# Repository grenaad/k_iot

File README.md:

View this project on [CADLAB.io](https://cadlab.io/project/23303). 

# k_iot
# k_iot

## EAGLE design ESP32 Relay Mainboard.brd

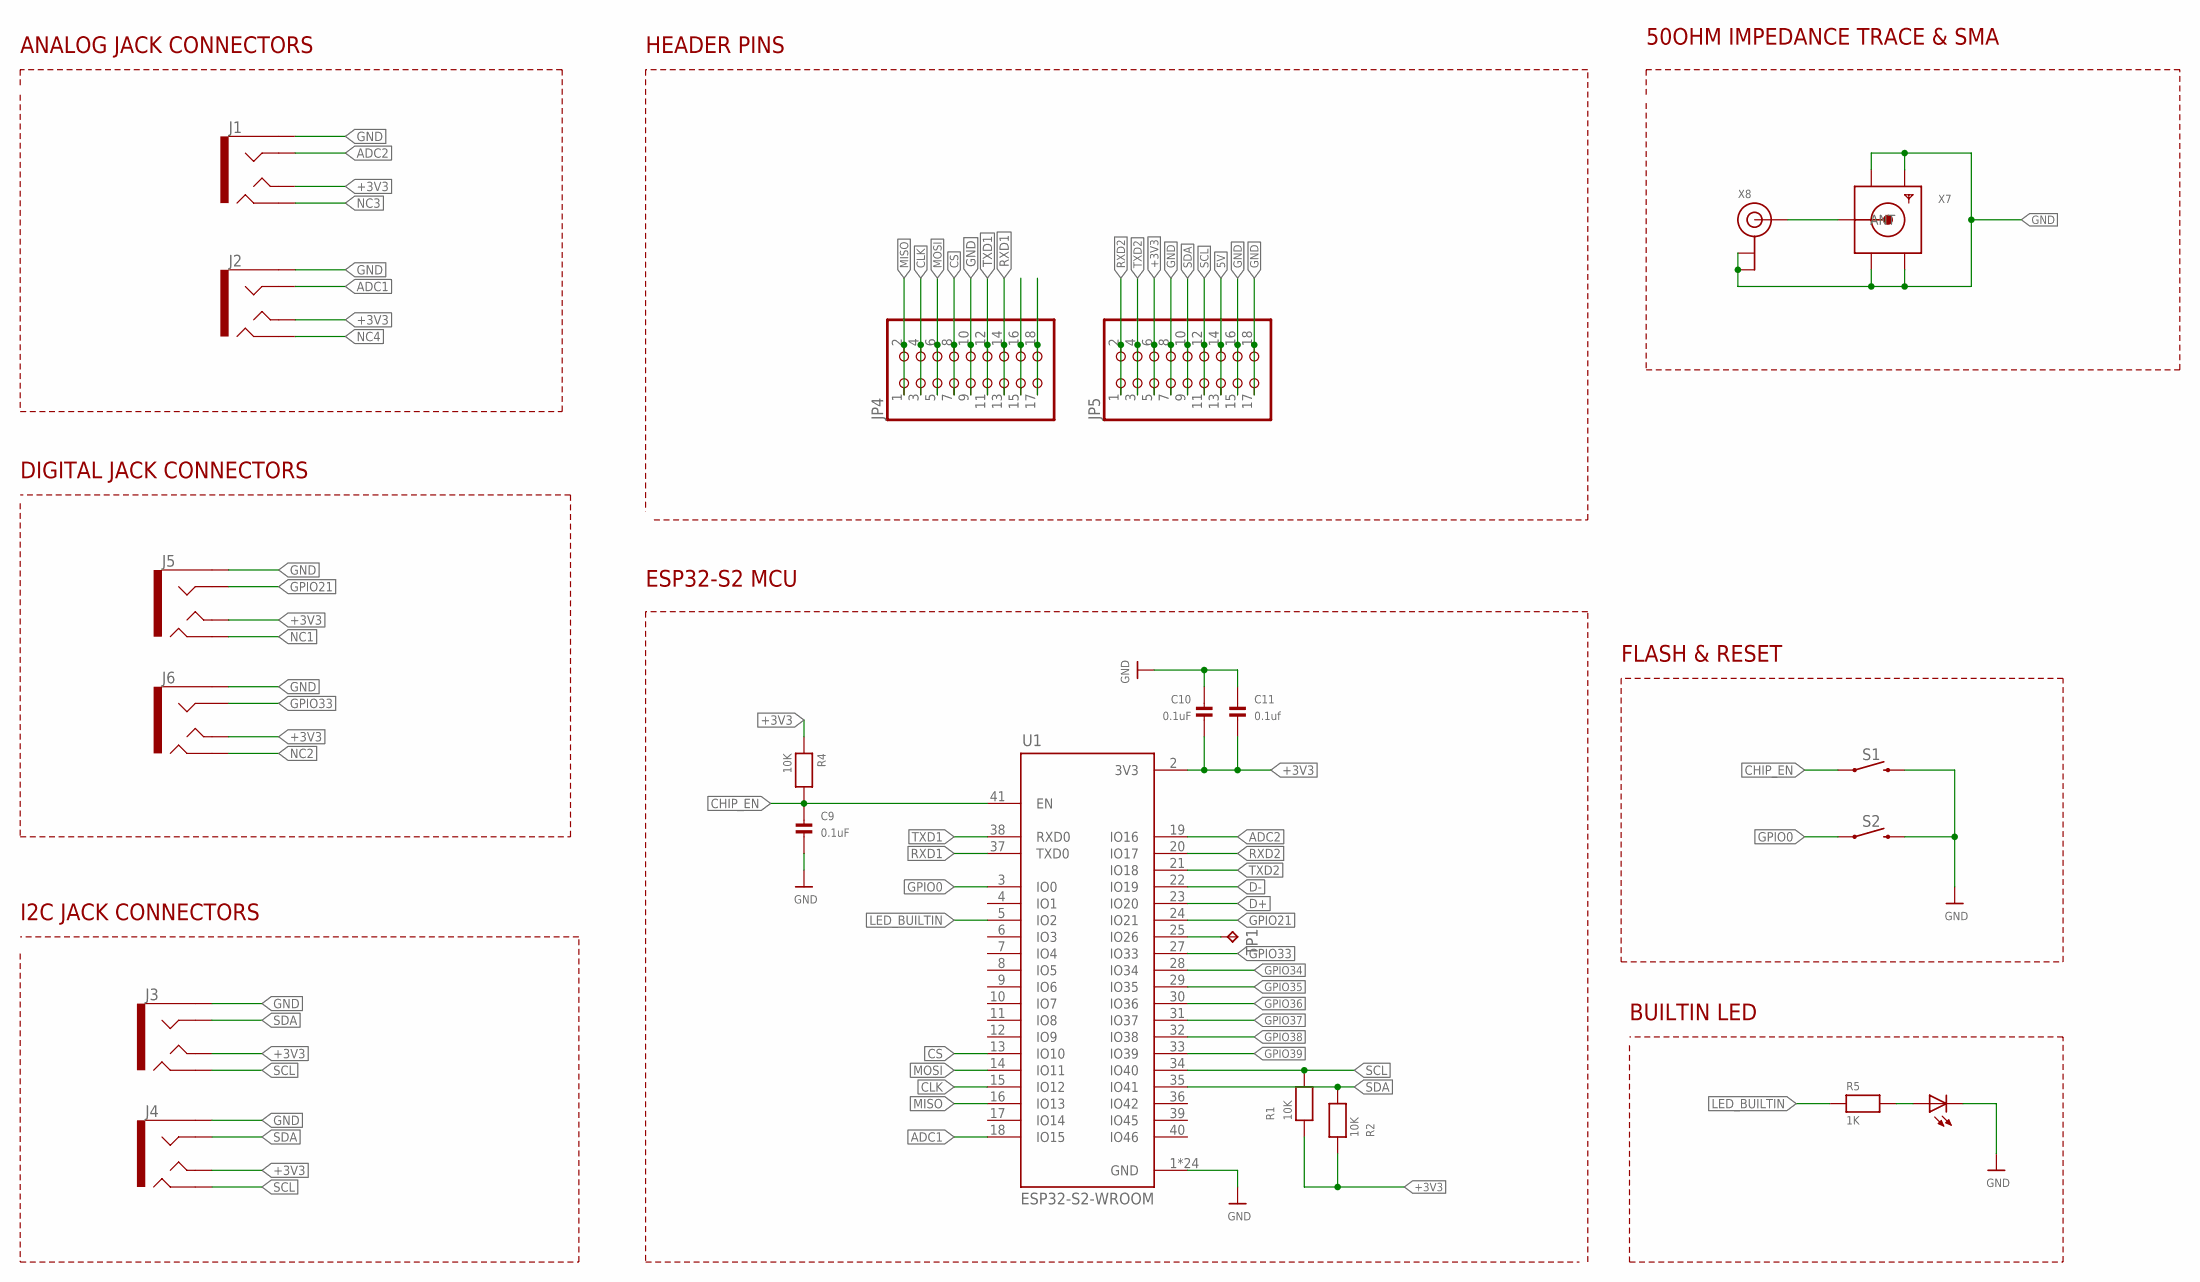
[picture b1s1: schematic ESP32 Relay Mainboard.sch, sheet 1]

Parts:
C9, C10: 0.1uF; 0805
C11: 0.1uf; 0805
J1, J2, J3, J4, J5, J6: AUDIO_JACK_TRRSSMD_RA; AUDIO_JACK_3.5MM_TRRS_SMD_RA
JP4, JP5: PINHD-2X9-BIG; 2X09-BIG
LED1: LEDCHIPLED_0805; CHIPLED_0805
R1, R2, R4: 10K; 0805
R5: 1K; 0805
S1, S2: MOMENTARY-SWITCH-SPST-SMD-5.2-REDUNDANT; TACTILE_SWITCH_SMD_5.2MM
TP1: TPTP20R; TP20R
U1: ESP32-S2-WROOM; XCVR_ESP32-S2-WROOM
X7: SMACONNECTOR_EDGE; SMA_EDGELAUNCH
X8: ANTENNA_U.FL; U.FL

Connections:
5V: JP5.13, JP5.14; also elsewhere on the board
+3V3: C10.2, C11.2, J1.TIP, J2.TIP, J3.TIP, J4.TIP, J5.TIP, J6.TIP, JP5.5, JP5.6, R1.1, R2.1, R4.1, U1.2 (3V3); also elsewhere on the board
ADC1: J2.RING1, U1.18 (IO15)
ADC2: J1.RING1, U1.19 (IO16)
CHIP_EN: C9.1, R4.2, S1.1, S1.2 (1), U1.41 (EN)
CLK: JP4.3, JP4.4, U1.15 (IO12)
CS: JP4.7, JP4.8, U1.13 (IO10)
D+: U1.23 (IO20); also elsewhere on the board
D-: U1.22 (IO19); also elsewhere on the board
GND: C9.2, C10.1, C11.1, J1.EARTH, J2.EARTH, J3.EARTH, J4.EARTH, J5.EARTH, J6.EARTH, JP4.9, JP4.10, JP5.7, JP5.8, JP5.15, JP5.16, JP5.17, JP5.18, LED1.C, S1.3 (2), S1.4 (2), S2.3 (2), S2.4 (2), U1.1 (GND), U1.26 (GND), U1.42 (GND), U1.43.1 (GND), U1.43.2 (GND), U1.43.3 (GND), U1.43.4 (GND), U1.43.5 (GND), U1.43.6 (GND), U1.43.7 (GND), U1.43.8 (GND), U1.43.9 (GND), U1.43.10 (GND), U1.43.11 (GND), U1.43.12 (GND), U1.43.13 (GND), U1.43.14 (GND), U1.43.15 (GND), U1.43.16 (GND), U1.43.17 (GND), U1.43.18 (GND), U1.43.19 (GND), U1.43.20 (GND), U1.43.21 (GND), X7.GND@1 (GND4), X7.GND@2 (GND3), X7.GND@3 (GND2), X7.GND@4 (GND1), X8.1 (GND), X8.2 (GND); also elsewhere on the board
GPIO0: S2.1, S2.2 (1), U1.3 (IO0)
GPIO21: J5.RING1, U1.24 (IO21)
GPIO33: J6.RING1, U1.27 (IO33)
GPIO34: U1.28 (IO34); also elsewhere on the board
GPIO35: U1.29 (IO35); also elsewhere on the board
GPIO36: U1.30 (IO36); also elsewhere on the board
GPIO37: U1.31 (IO37); also elsewhere on the board
GPIO38: U1.32 (IO38); also elsewhere on the board
GPIO39: U1.33 (IO39); also elsewhere on the board
LED_BUILTIN: R5.1, U1.5 (IO2)
MISO: JP4.1, JP4.2, U1.16 (IO13)
MOSI: JP4.5, JP4.6, U1.14 (IO11)
unnamed: LED1.A, R5.2
unnamed: X7.P (ANT), X8.3 (SIGNAL)
unnamed: TP1.TP, U1.25 (IO26)
unnamed: JP4.15, JP4.16
unnamed: JP4.17, JP4.18
NC1: J5.RING2
NC2: J6.RING2
NC3: J1.RING2
NC4: J2.RING2
RXD1: JP4.13, JP4.14, U1.37 (TXD0)
RXD2: JP5.1, JP5.2, U1.20 (IO17)
SCL: J3.RING2, J4.RING2, JP5.11, JP5.12, R1.2, U1.34 (IO40)
SDA: J3.RING1, J4.RING1, JP5.9, JP5.10, R2.2, U1.35 (IO41)
TXD1: JP4.11, JP4.12, U1.38 (RXD0)
TXD2: JP5.3, JP5.4, U1.21 (IO18)

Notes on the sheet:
FLASH & RESET
BUILTIN LED
50OHM IMPEDANCE TRACE & SMA
ESP32-S2 MCU
I2C JACK CONNECTORS
DIGITAL JACK CONNECTORS
ANALOG JACK CONNECTORS
HEADER PINS

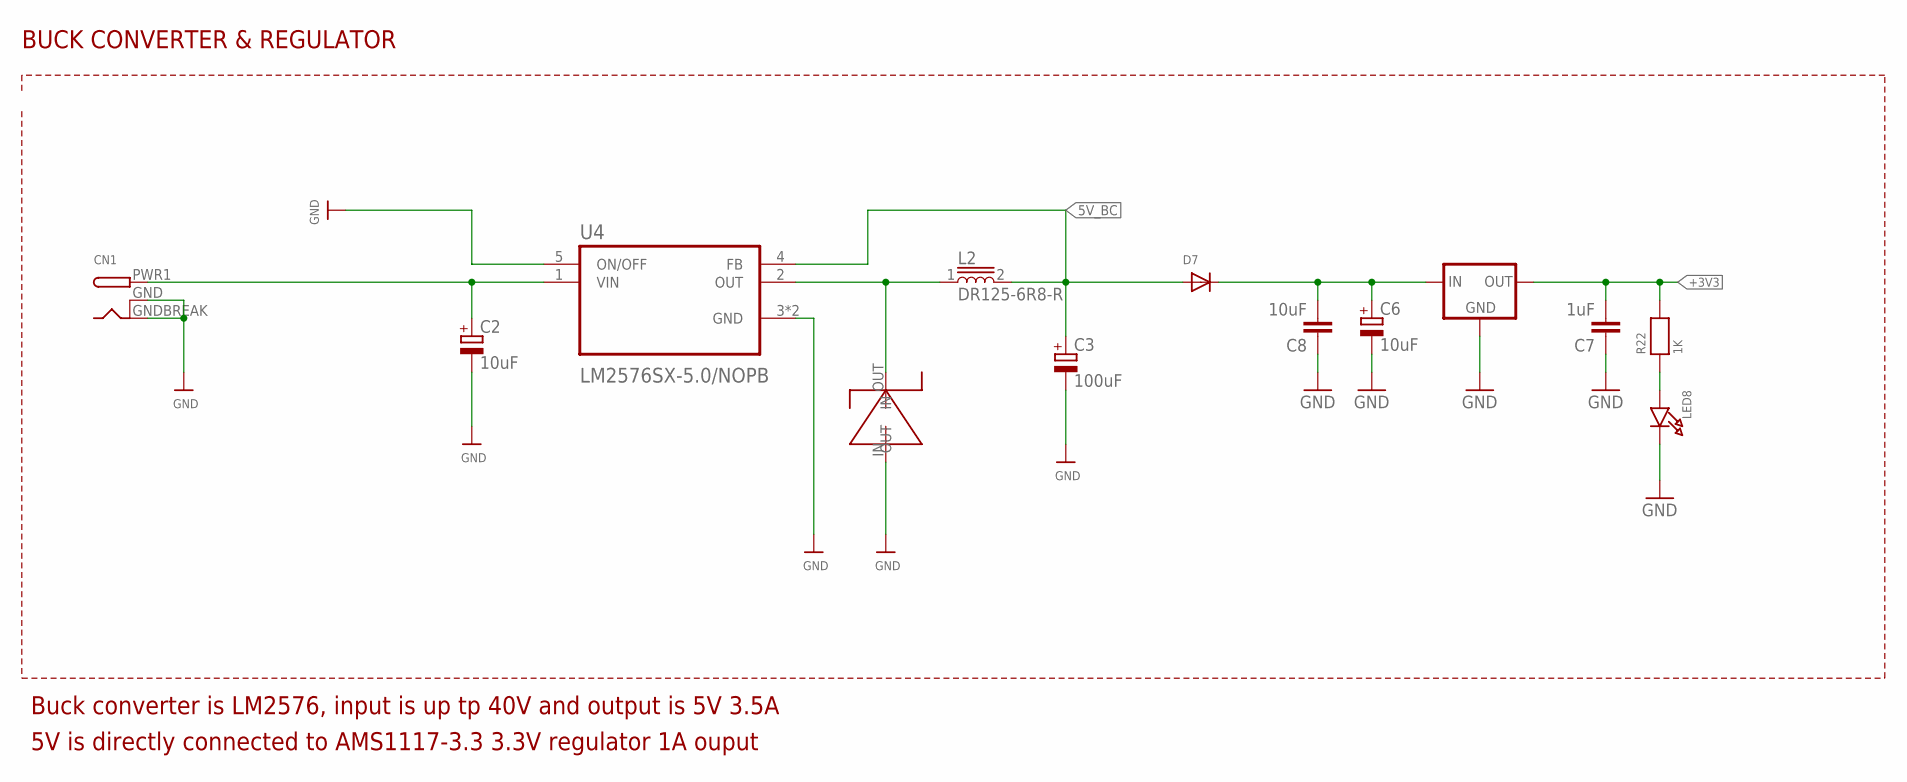
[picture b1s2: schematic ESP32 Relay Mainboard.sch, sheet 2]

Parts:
3.3V: LM1117; SOT223
C2: 10uF; UD-8X10_NICHICON
C3: 100uF; UD-10X10_NICHICON
C6: 10uF; UD-5X5,8_NICHICON
C7: 1uF; 0805
C8: 10uF; 0805
CN1: DCBARRELSMT; DCJACK_2MM_SMT
D7: DIODESMA; SMADIODE
L2: DR125-6R8-R; INDM1250X1250X600
LED8: LED0805; CHIPLED_0805
R22: 1K; 0805
U4: LM2576SX-5.0/NOPB; VREG_TPS79625KTTR
U$8: DO-214AB

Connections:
5V: 3.3V.3 (IN), C6.+, C8.2, D7.C; also elsewhere on the board
5V_BC: C3.+, D7.A, L2.2, U4.4 (FB)
+3V3: 3.3V.2 (OUT), C7.2, R22.2; also elsewhere on the board
GND: 3.3V.1 (GND), C2.-, C3.-, C6.-, C7.1, C8.1, CN1.GND (GNDBREAK), CN1.GNDBREAK (GND), LED8.C, U4.3 (GND), U4.5 (ON/OFF), U4.6 (GND), U$8.IN; also elsewhere on the board
unnamed: C2.+, CN1.PWR1 (PWR), U4.1 (VIN)
unnamed: L2.1, U4.2 (OUT), U$8.OUT
unnamed: LED8.A, R22.1

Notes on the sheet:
BUCK CONVERTER & REGULATOR
Buck converter is LM2576, input is up tp 40V and output is 5V 3.5A
5V is directly connected to AMS1117-3.3 3.3V regulator 1A ouput

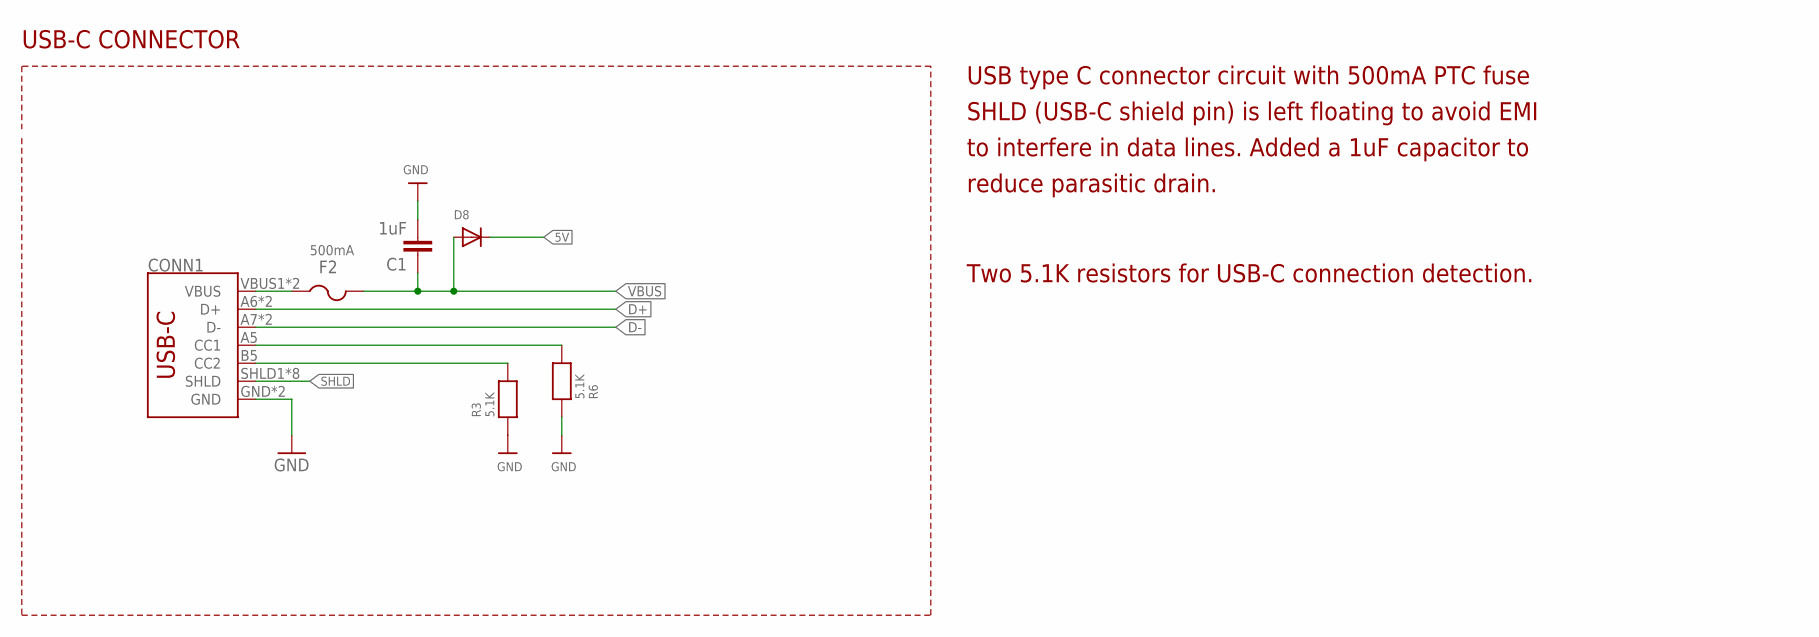
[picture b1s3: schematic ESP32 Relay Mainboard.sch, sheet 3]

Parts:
C1: 1uF; 0805
CONN1: USB_C16PIN; USB-C-16P
D8: DIODESOD-123; SOD-123
F2: PTCFUSE-1206; R1206
R3, R6: 5.1K; 0603

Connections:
5V: D8.C; also elsewhere on the board
D+: CONN1.A6 (D+), CONN1.B6 (D+); also elsewhere on the board
D-: CONN1.A7 (D-), CONN1.B7 (D-); also elsewhere on the board
GND: C1.2, CONN1.GND, CONN1.GND2 (GND), R3.1, R6.1; also elsewhere on the board
unnamed: CONN1.A5 (CC1), R6.2
unnamed: CONN1.B5 (CC2), R3.2
SHLD: CONN1.SHLD1 (SHLD), CONN1.SHLD2 (SHLD), CONN1.SHLD3 (SHLD), CONN1.SHLD4 (SHLD), CONN1.SHLD5 (SHLD), CONN1.SHLD6 (SHLD), CONN1.SHLD7 (SHLD), CONN1.SHLD8 (SHLD)
VBUS: C1.1, D8.A, F2.2
X_VBUS: CONN1.VBUS1 (VBUS), CONN1.VBUS2 (VBUS), F2.1

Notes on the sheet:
500mA
USB-C CONNECTOR
USB type C connector circuit with 500mA PTC fuse
SHLD (USB-C shield pin) is left floating to avoid EMI
to interfere in data lines. Added a 1uF capacitor to
reduce parasitic drain.
Two 5.1K resistors for USB-C connection detection.

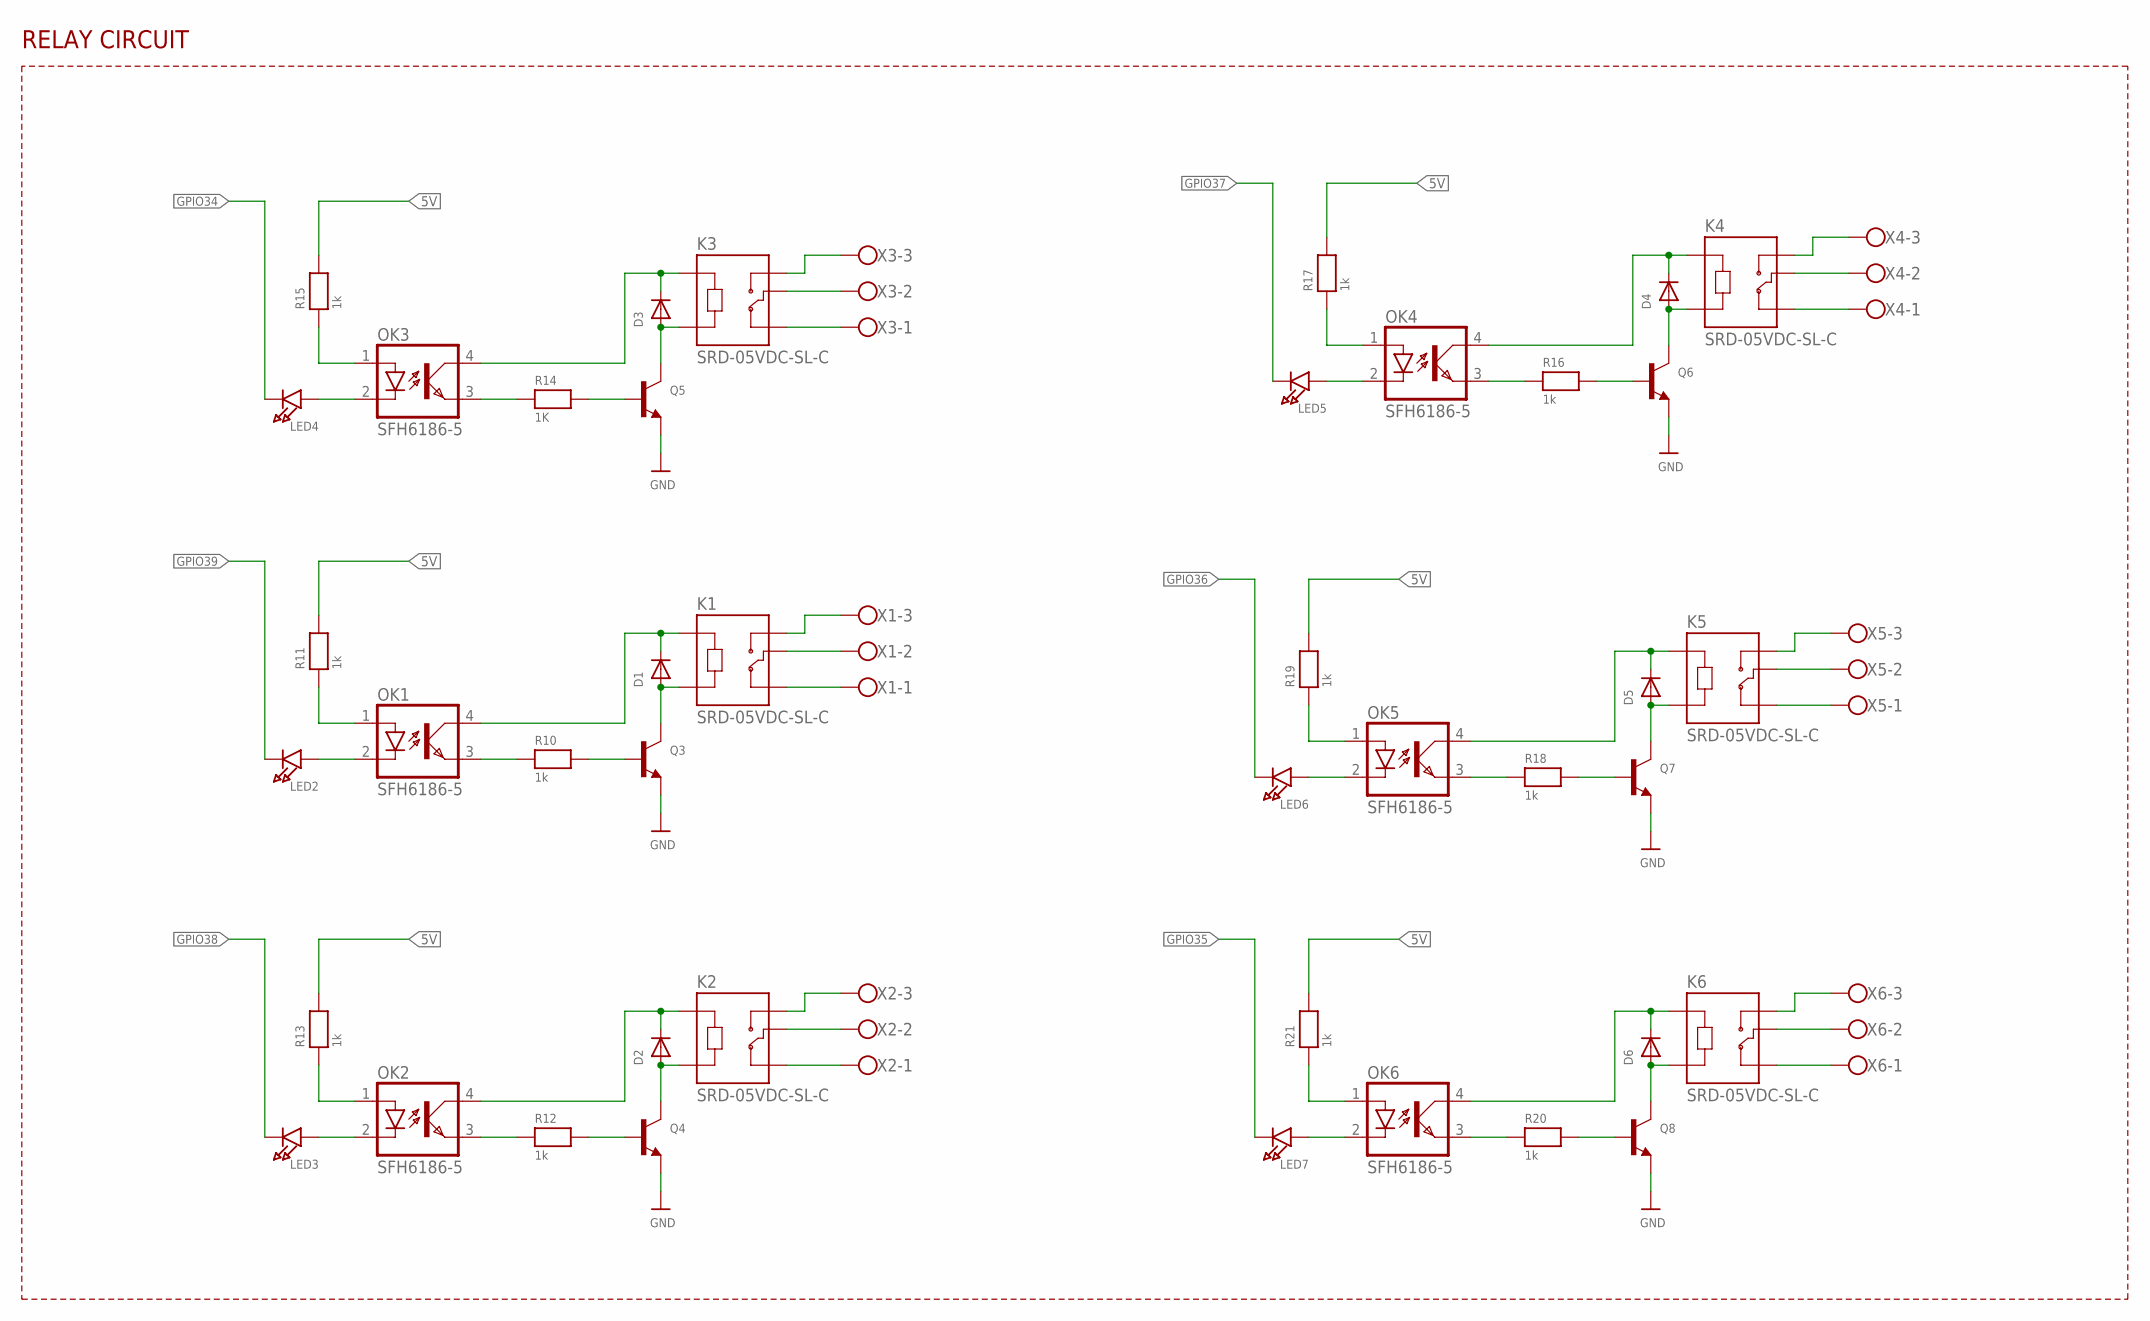
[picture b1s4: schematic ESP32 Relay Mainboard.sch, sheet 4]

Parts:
D1, D2, D3, D4, D5, D6: DIODESMA; SMADIODE
K1, K2, K3, K4, K5, K6: SRD-05VDC-SL-C; RELAY_SRD-05VDC-SL-C
LED2, LED3, LED4, LED5, LED6, LED7: LED0805; CHIPLED_0805
OK1, OK2, OK3, OK4, OK5, OK6: SFH6186-5; SMD4-7
Q3, Q4, Q5, Q6, Q7, Q8: TRANSISTOR_NPN; SOT23-R
R10, R11, R12, R13, R15, R16, R17, R18, R19, R20, R21: 1k; 0805
R14: 1K; 0805
X1, X2, X3, X4, X5, X6: W237-103

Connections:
5V: R11.2, R13.2, R15.2, R17.2, R19.2, R21.2; also elsewhere on the board
GND: Q3.2 (E), Q4.2 (E), Q5.2 (E), Q6.2 (E), Q7.2 (E), Q8.2 (E); also elsewhere on the board
GPIO34: LED4.C; also elsewhere on the board
GPIO35: LED7.C; also elsewhere on the board
GPIO36: LED6.C; also elsewhere on the board
GPIO37: LED5.C; also elsewhere on the board
GPIO38: LED3.C; also elsewhere on the board
GPIO39: LED2.C; also elsewhere on the board
unnamed: OK1.1 (A), R11.1
unnamed: LED2.A, OK1.2 (C)
unnamed: OK1.3 (EMIT), R10.1
unnamed: Q3.1 (B), R10.2
unnamed: D1.A, K1.A2, Q3.3 (C)
unnamed: D1.C, K1.A1, OK1.4 (COL)
unnamed: K1.NO, X1.3
unnamed: K1.COM, X1.2
unnamed: K1.NC, X1.1
unnamed: OK2.1 (A), R13.1
unnamed: LED3.A, OK2.2 (C)
unnamed: OK2.3 (EMIT), R12.1
unnamed: Q4.1 (B), R12.2
unnamed: D2.A, K2.A2, Q4.3 (C)
unnamed: D2.C, K2.A1, OK2.4 (COL)
unnamed: K2.NO, X2.3
unnamed: K2.COM, X2.2
unnamed: K2.NC, X2.1
unnamed: OK3.1 (A), R15.1
unnamed: LED4.A, OK3.2 (C)
unnamed: OK3.3 (EMIT), R14.1
unnamed: Q5.1 (B), R14.2
unnamed: D3.A, K3.A2, Q5.3 (C)
unnamed: D3.C, K3.A1, OK3.4 (COL)
unnamed: K3.NO, X3.3
unnamed: K3.COM, X3.2
unnamed: K3.NC, X3.1
unnamed: OK4.1 (A), R17.1
unnamed: LED5.A, OK4.2 (C)
unnamed: OK4.3 (EMIT), R16.1
unnamed: Q6.1 (B), R16.2
unnamed: D4.A, K4.A2, Q6.3 (C)
unnamed: D4.C, K4.A1, OK4.4 (COL)
unnamed: K4.NO, X4.3
unnamed: K4.COM, X4.2
unnamed: K4.NC, X4.1
unnamed: OK5.1 (A), R19.1
unnamed: LED6.A, OK5.2 (C)
unnamed: OK5.3 (EMIT), R18.1
unnamed: Q7.1 (B), R18.2
unnamed: D5.A, K5.A2, Q7.3 (C)
unnamed: D5.C, K5.A1, OK5.4 (COL)
unnamed: K5.NO, X5.3
unnamed: K5.COM, X5.2
unnamed: K5.NC, X5.1
unnamed: OK6.1 (A), R21.1
unnamed: LED7.A, OK6.2 (C)
unnamed: OK6.3 (EMIT), R20.1
unnamed: Q8.1 (B), R20.2
unnamed: D6.A, K6.A2, Q8.3 (C)
unnamed: D6.C, K6.A1, OK6.4 (COL)
unnamed: K6.NO, X6.3
unnamed: K6.COM, X6.2
unnamed: K6.NC, X6.1

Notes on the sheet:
RELAY CIRCUIT

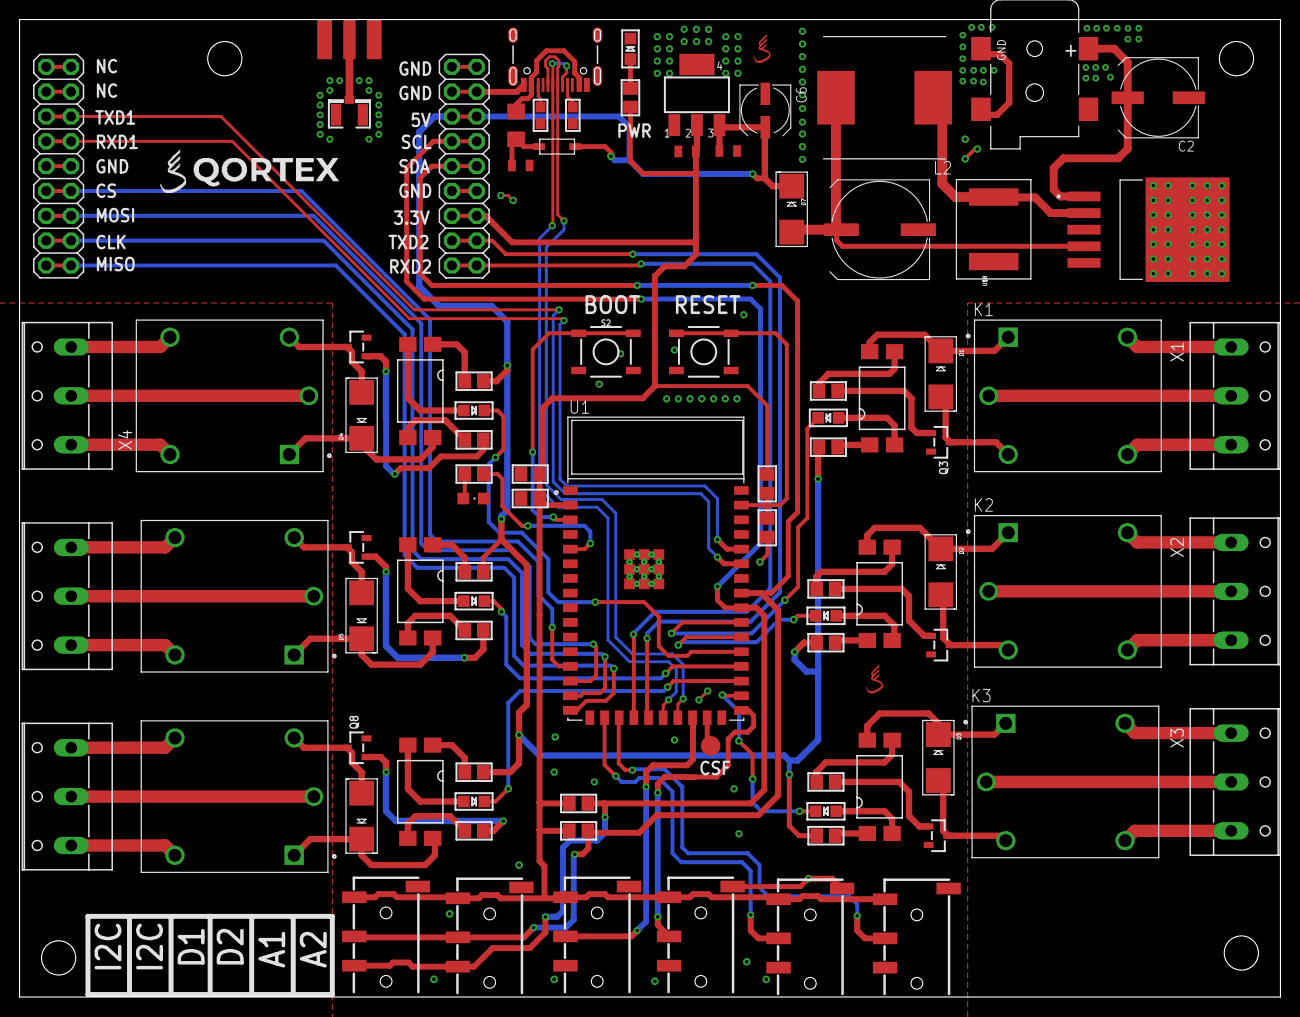
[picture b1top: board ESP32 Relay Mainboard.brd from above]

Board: 2 copper layers, 129.0 x 100.0 mm, 92 parts (0 on the bottom side), 96 nets.

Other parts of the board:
U$1: QORTEX_00#PNG
U$25, U$27: QORTEX_ICON_PROTOTYPE_01#PNG

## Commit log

2020-09-11 Backlink to CADLAB.io has been added.
2020-09-18 First commit
    Board with 5 jack connectors all of them I2C. Will do second commit with 2 Analogs, 2 Digital and 2 I2C
2020-09-18 Rendered pcb / First version
2020-09-29 Add files via upload
    Added second UART port. Added OTG usb. Removed CP2102. Added 6th jack connector. Added labels.
2020-10-06 Updated the schematic with values
    Added values to components (resistors and caps). Also added a description to some parts of the board.
2020-11-11 Add files via upload
    Removed optocouplers. added AZ1045 ESD protection array to D+ and D- lines
2020-11-21 Add files via upload
    Added SMD Varistor. Minor changes. Chnaged capacitor values to 1000uf on step down converter and 100uf on 3.3v regulator

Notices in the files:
parts and their libraries:
SparkFun-Connectors: Licensing: Creative Commons ShareAlike 4.0 International - https://creativecommons.org/licenses/by-sa/4.0
microbuilder: This work is placed in the public domain, and may be freely used for commercial and non-commercial work with the following conditions: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
